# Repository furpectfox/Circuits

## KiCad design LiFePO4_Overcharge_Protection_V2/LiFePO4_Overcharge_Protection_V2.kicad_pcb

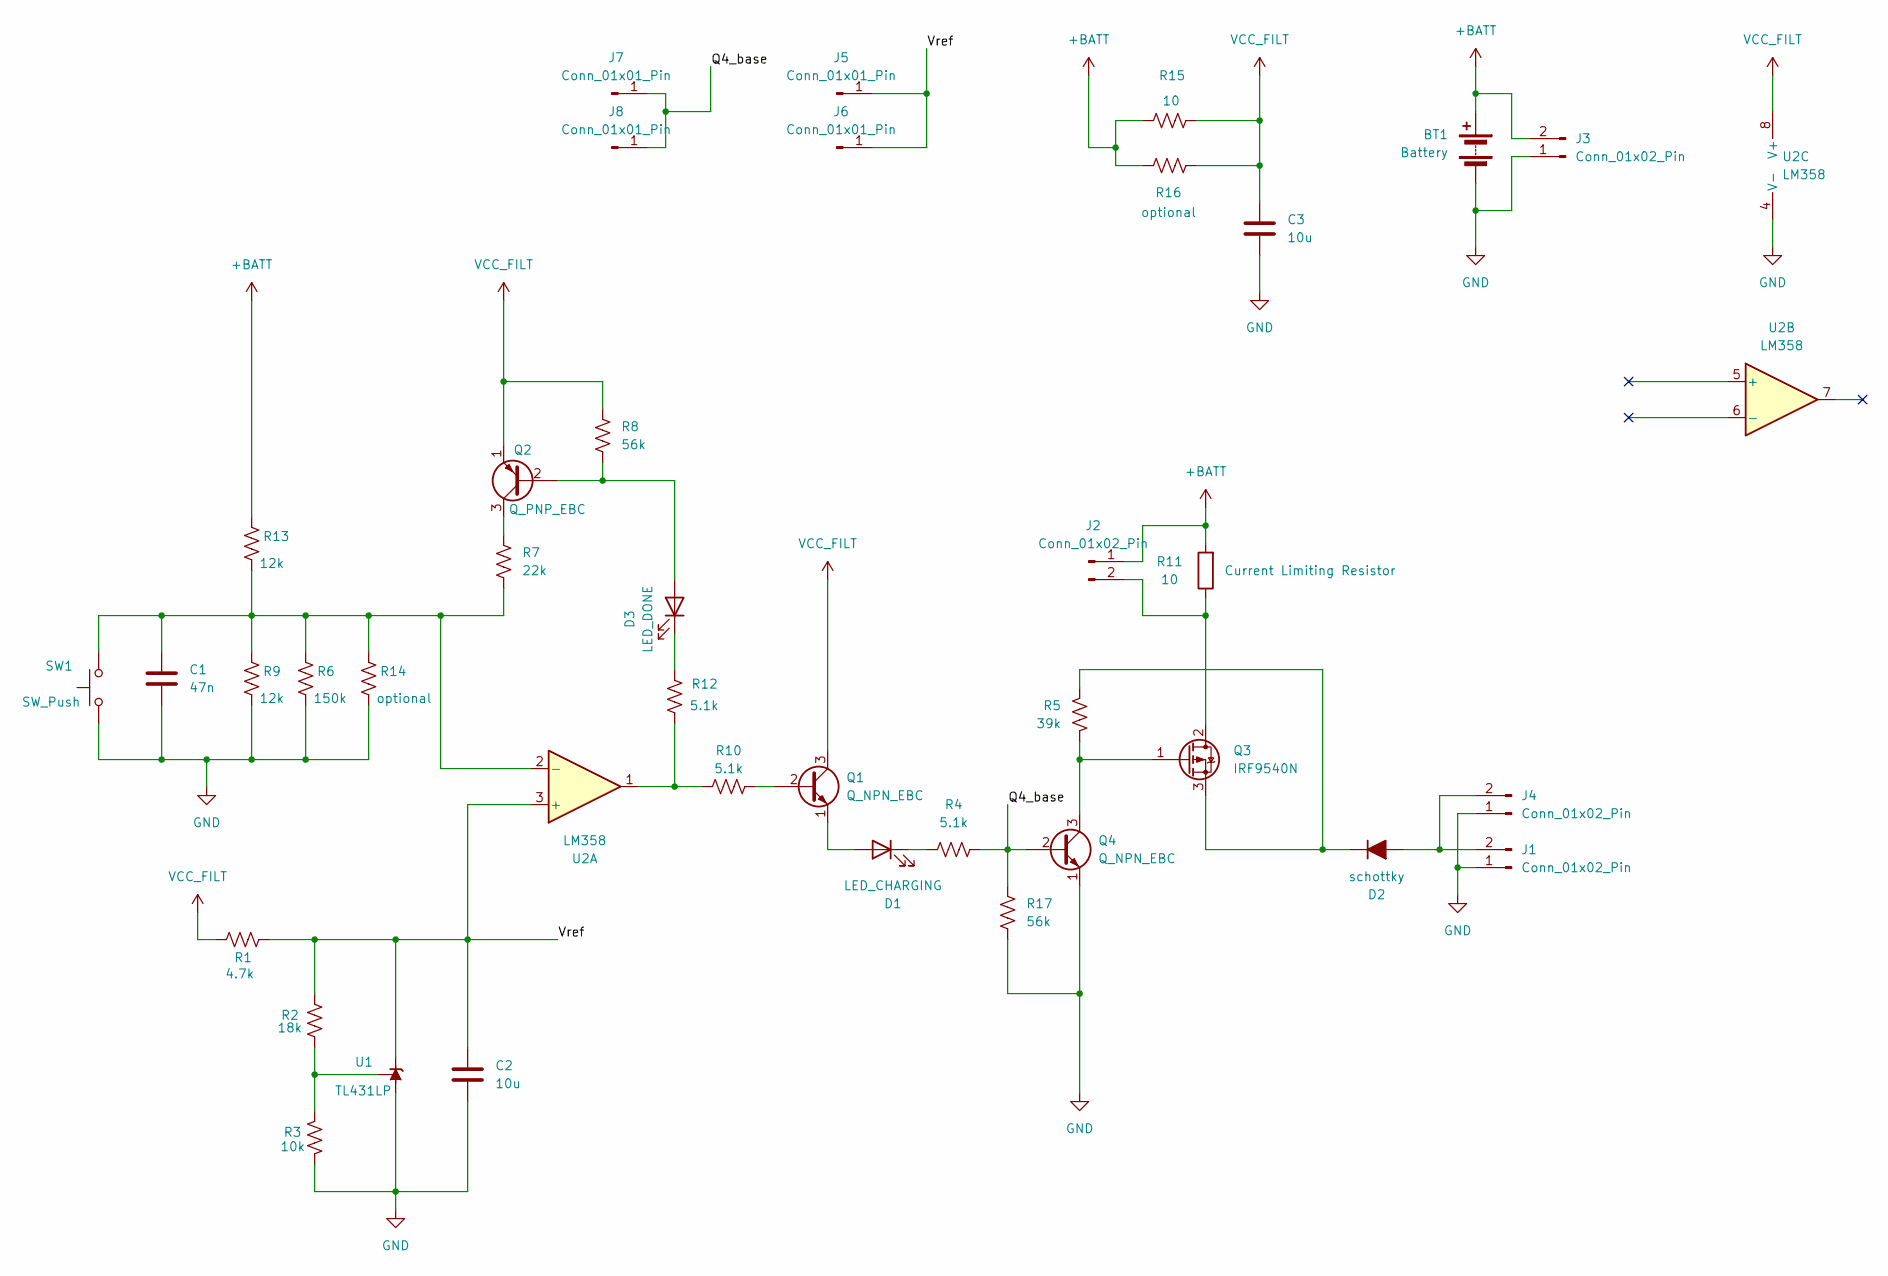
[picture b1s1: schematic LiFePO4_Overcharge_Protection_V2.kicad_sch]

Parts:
BT1: Battery; TestPoint_2Pads_Pitch5.08mm_Drill1.3mm
C1: 47n; C_Disc_D4.7mm_W2.5mm_P5.00mm
C2, C3: 10u; C_Disc_D4.7mm_W2.5mm_P5.00mm
D1: LED_CHARGING; LED_D5.0mm_Clear
D2: schottky; D_DO-27_P15.24mm_Horizontal
D3: LED_DONE; LED_D5.0mm_Clear
J1, J2, J3, J4: Conn_01x02_Pin; TestPoint_2Pads_Pitch5.08mm_Drill1.3mm
J5, J6, J7, J8: Conn_01x01_Pin; SolderWire-0.1sqmm_1x01_D0.4mm_OD1mm
Q1, Q4: Q_NPN_EBC; TO-92L_Inline_Wide
Q2: Q_PNP_EBC; TO-92L_Inline_Wide
Q3: IRF9540N; TO-220-3_Vertical
R1: 4.7k; R_Axial_DIN0207_L6.3mm_D2.5mm_P7.62mm_Horizontal
R2: 18k; R_Axial_DIN0207_L6.3mm_D2.5mm_P7.62mm_Horizontal
R3: 10k; R_Axial_DIN0207_L6.3mm_D2.5mm_P7.62mm_Horizontal
R4, R12: 5.1k; R_Axial_DIN0207_L6.3mm_D2.5mm_P7.62mm_Horizontal
R5: 39k; R_Axial_DIN0207_L6.3mm_D2.5mm_P7.62mm_Horizontal
R6: 150k; R_Axial_DIN0207_L6.3mm_D2.5mm_P7.62mm_Horizontal
R7: 22k; R_Axial_DIN0207_L6.3mm_D2.5mm_P7.62mm_Horizontal
R8, R17: 56k; R_Axial_DIN0207_L6.3mm_D2.5mm_P7.62mm_Horizontal
R9, R13: 12k; R_Axial_DIN0207_L6.3mm_D2.5mm_P7.62mm_Horizontal
R10: 5.1k; R_Axial_DIN0207_L6.3mm_D2.5mm_P10.16mm_Horizontal
R11: 10; TestPoint_2Pads_Pitch5.08mm_Drill1.3mm
R14, R16: optional; R_Axial_DIN0207_L6.3mm_D2.5mm_P7.62mm_Horizontal
R15: 10; R_Axial_DIN0207_L6.3mm_D2.5mm_P7.62mm_Horizontal
SW1: SW_Push
U1: TL431LP; TO-92L_Inline_Wide
U2: LM358; DIP-8_W7.62mm_LongPads

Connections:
+BATT: BT1.1 (+), J2.1, J3.2, R11.2, R13.1, R15.1, R16.1
/Q4_base: J7.1, J8.1, Q4.2 (B), R4.2, R17.1
/Vref: C2.1, J5.1, J6.1, R1.1, R2.1, U1.3 (K), U2.3 (+)
GND: BT1.2 (-), C1.2, C2.2, C3.2, J1.1, J3.1, J4.1, Q4.1 (E), R3.2, R6.2, R9.2, R14.2, R17.2, SW1.1, U1.2 (A), U2.4 (V-)
unnamed: D1.2 (A), Q1.1 (E)
unnamed: D1.1 (K), R4.1
unnamed: D2.2 (A), J1.2, J4.2
unnamed: D2.1 (K), Q3.3 (S), R5.2
unnamed: D3.2 (A), Q2.2 (B), R8.2
unnamed: D3.1 (K), R12.2
unnamed: J2.2, Q3.2 (D), R11.1
unnamed: Q1.2 (B), R10.2
unnamed: Q2.3 (C), R7.1
unnamed: Q3.1 (G), Q4.3 (C), R5.1
unnamed: R10.1, R12.1, U2.1
unnamed: R2.2, R3.1, U1.1 (REF)
unnamed: C1.1, R6.1, R7.2, R9.1, R13.2, R14.1, SW1.2, U2.2 (-)
VCC_FILT: C3.1, Q1.3 (C), Q2.1 (E), R1.2, R8.1, R15.2, R16.2, U2.8 (V+)

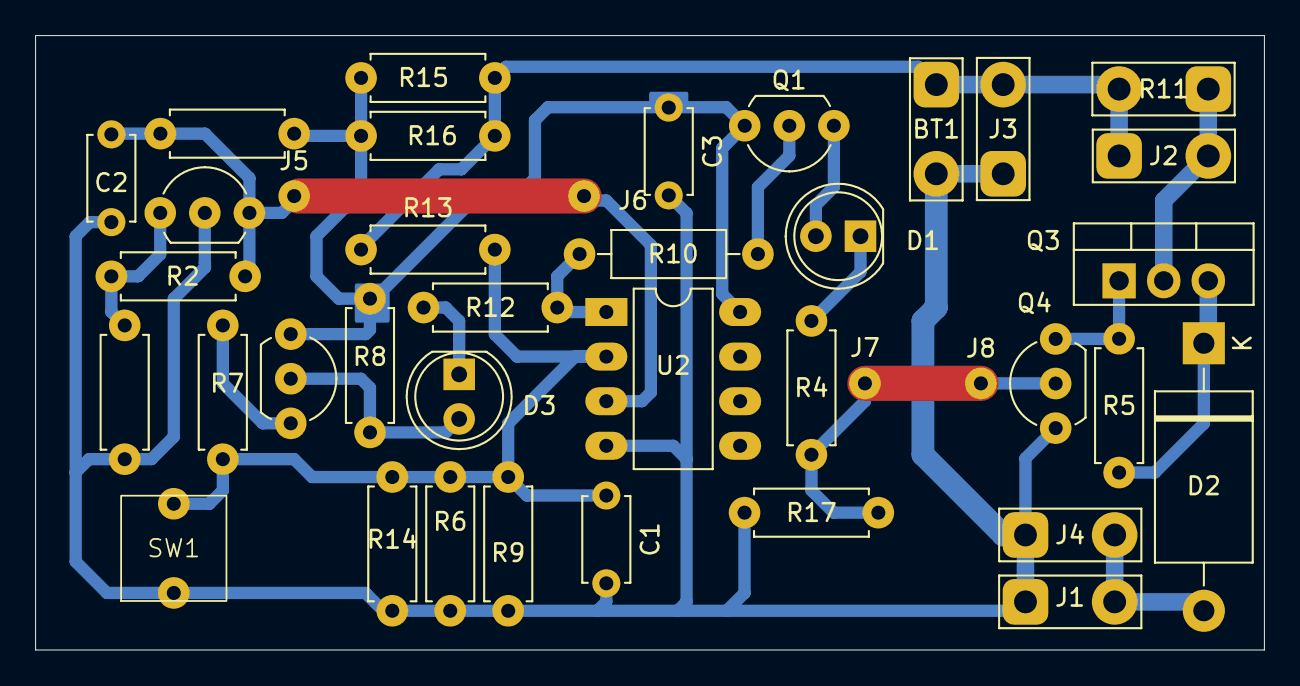
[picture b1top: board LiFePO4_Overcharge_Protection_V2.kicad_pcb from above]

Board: 2 copper layers, 70.0 x 35.0 mm, 39 parts (0 on the bottom side), 18 nets.

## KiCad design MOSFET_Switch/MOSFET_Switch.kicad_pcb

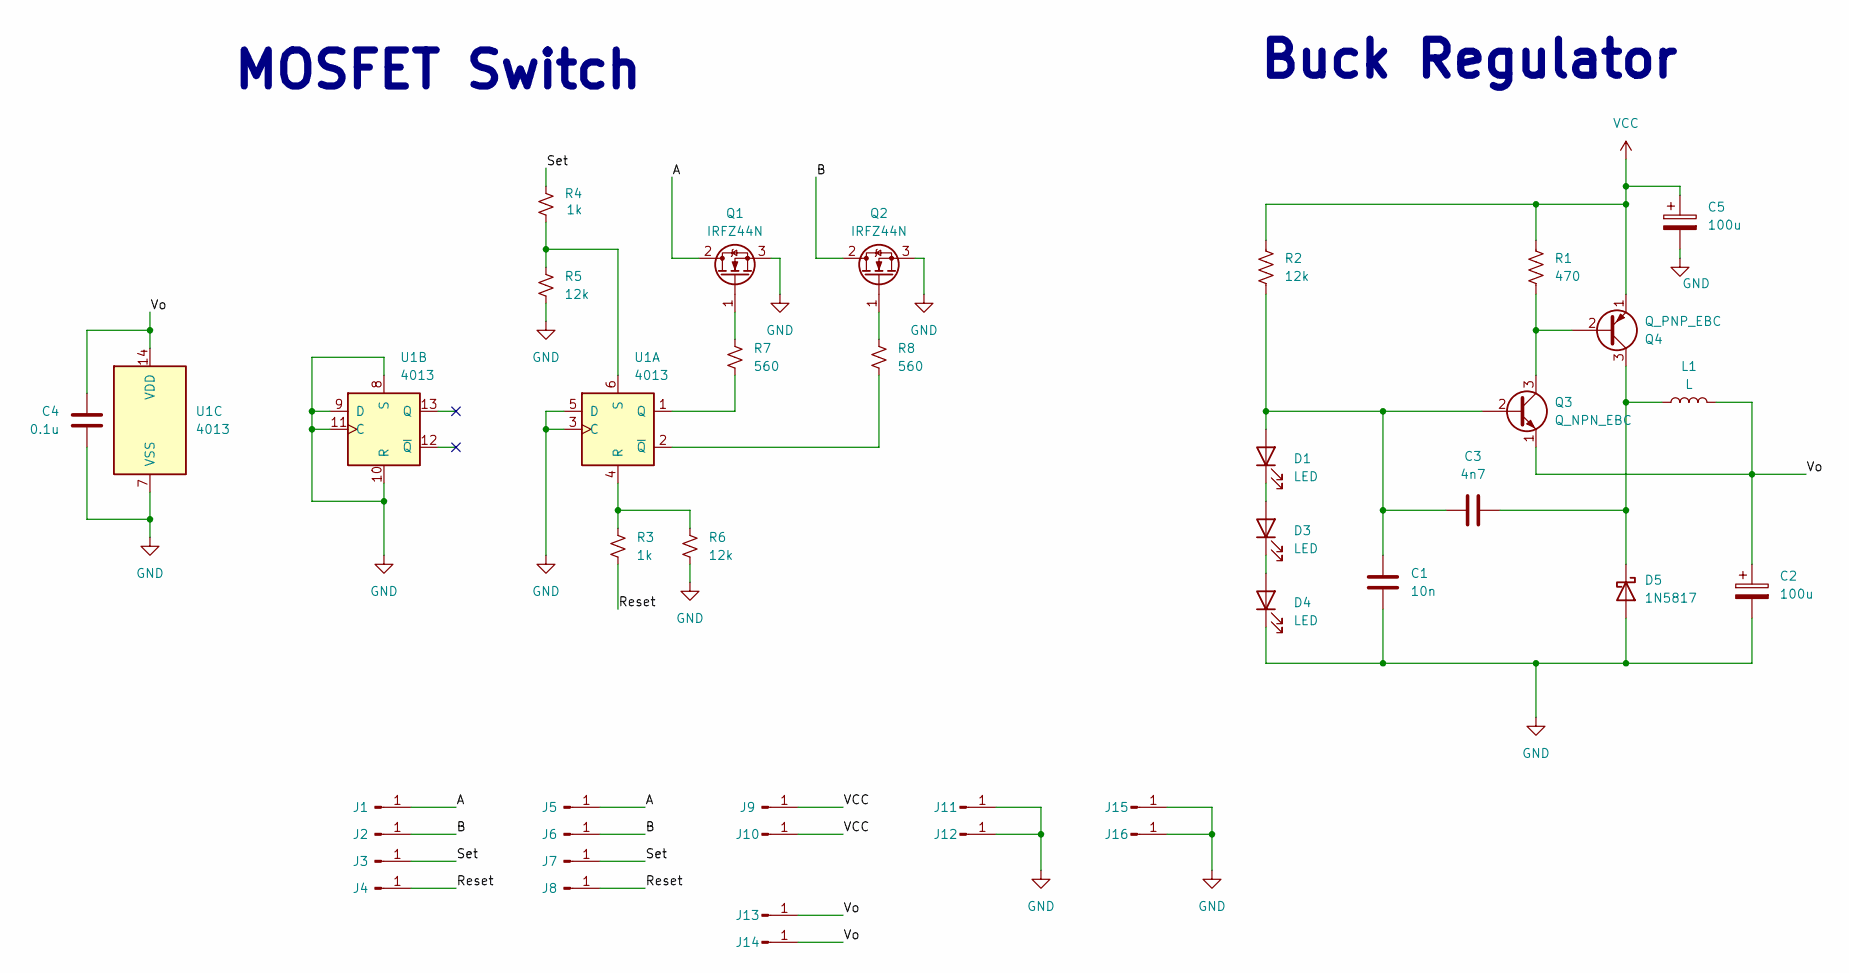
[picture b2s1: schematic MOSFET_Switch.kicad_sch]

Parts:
C1: 10n; C_Disc_D5.1mm_W3.2mm_P5.00mm
C2, C5: 100u; CP_Radial_D5.0mm_P2.50mm
C3: 4n7; C_Disc_D5.1mm_W3.2mm_P5.00mm
C4: 0.1u; C_Disc_D5.1mm_W3.2mm_P5.00mm
D1, D3, D4: LED; LED_D5.0mm
D5: 1N5817; D_DO-41_SOD81_P10.16mm_Horizontal
J1, J2, J3, J4, J5, J6, J7, J8, J9, J10, J11, J12, J13, J14, J15, J16: Conn_01x01_Pin; SolderWire-0.1sqmm_1x01_D0.4mm_OD1mm
L1: L; L_Radial_D7.0mm_P3.00mm
Q1, Q2: IRFZ44N; TO-220-3_Vertical
Q3: Q_NPN_EBC; TO-92L_Inline_Wide
Q4: Q_PNP_EBC; TO-92L_Inline_Wide
R1: 470; R_Axial_DIN0207_L6.3mm_D2.5mm_P7.62mm_Horizontal
R2: 12k; R_Axial_DIN0207_L6.3mm_D2.5mm_P7.62mm_Horizontal
R3, R4: 1k; R_0603_1608Metric_Pad0.98x0.95mm_HandSolder
R5, R6: 12k; R_0603_1608Metric_Pad0.98x0.95mm_HandSolder
R7, R8: 560; R_0603_1608Metric_Pad0.98x0.95mm_HandSolder
U1: 4013; DIP-14_W7.62mm_LongPads

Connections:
/A: J1.1, J5.1, Q1.2 (D)
/B: J2.1, J6.1, Q2.2 (D)
/Reset: J4.1, J8.1, R3.2
/Set: J3.1, J7.1, R4.1
/Vo: C2.1, C4.1, J13.1, J14.1, L1.2, Q3.1 (E), U1.14 (VDD)
GND: C1.2, C2.2, C4.2, C5.2, D4.1 (K), D5.2 (A), J11.1, J12.1, J15.1, J16.1, Q1.3 (S), Q2.3 (S), R5.2, R6.2, U1.3 (C), U1.5 (D), U1.7 (VSS), U1.8 (S), U1.9 (D), U1.10 (R), U1.11 (C)
unnamed: C1.1, C3.1, D1.2 (A), Q3.2 (B), R2.2
unnamed: D1.1 (K), D3.2 (A)
unnamed: D3.1 (K), D4.2 (A)
unnamed: C3.2, D5.1 (K), L1.1, Q4.3 (C)
unnamed: Q1.1 (G), R7.1
unnamed: Q2.1 (G), R8.1
unnamed: Q3.3 (C), Q4.2 (B), R1.2
unnamed: R7.2, U1.1 (Q)
unnamed: R3.1, R6.1, U1.4 (R)
unnamed: R4.2, R5.1, U1.6 (S)
unnamed: R8.2, U1.2 (~Q)
VCC: C5.1, J9.1, J10.1, Q4.1 (E), R1.1, R2.1

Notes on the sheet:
Buck Regulator
MOSFET Switch

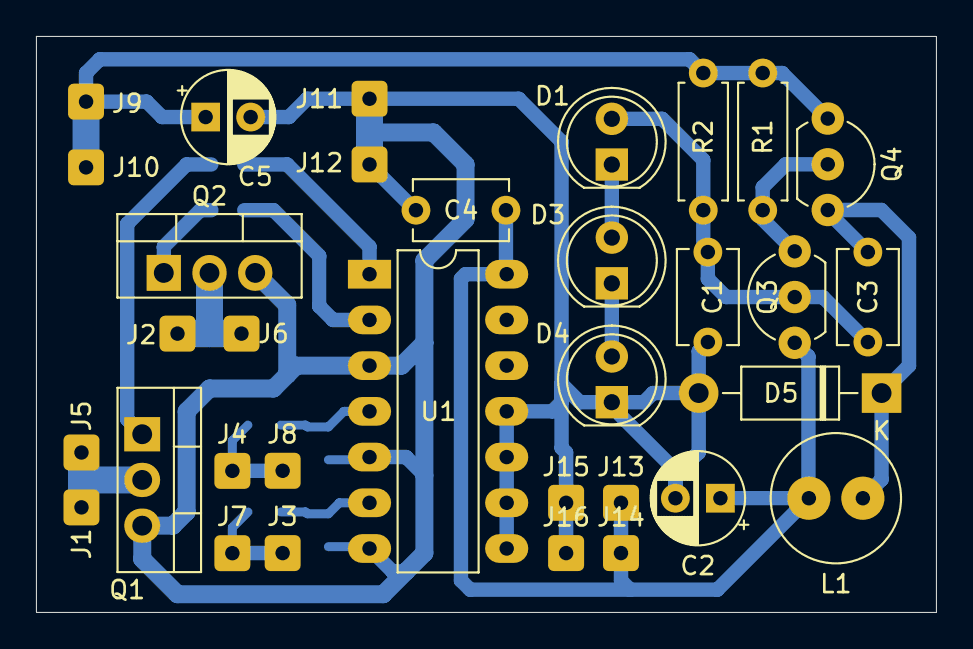
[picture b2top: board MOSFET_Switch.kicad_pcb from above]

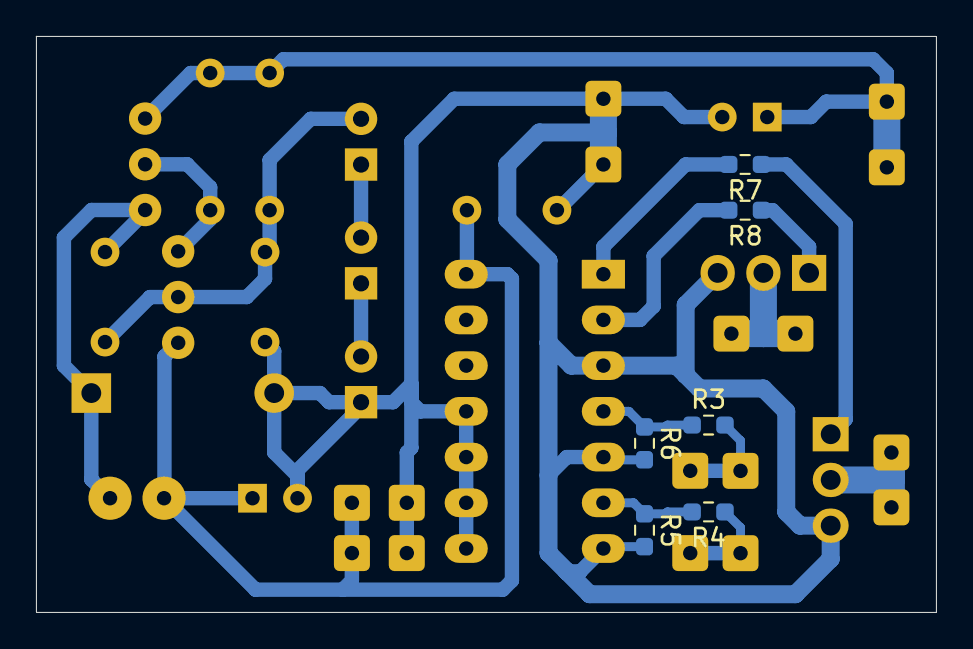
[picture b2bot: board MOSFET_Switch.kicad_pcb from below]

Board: 2 copper layers, 50.0 x 32.0 mm, 39 parts (6 on the bottom side), 18 nets.

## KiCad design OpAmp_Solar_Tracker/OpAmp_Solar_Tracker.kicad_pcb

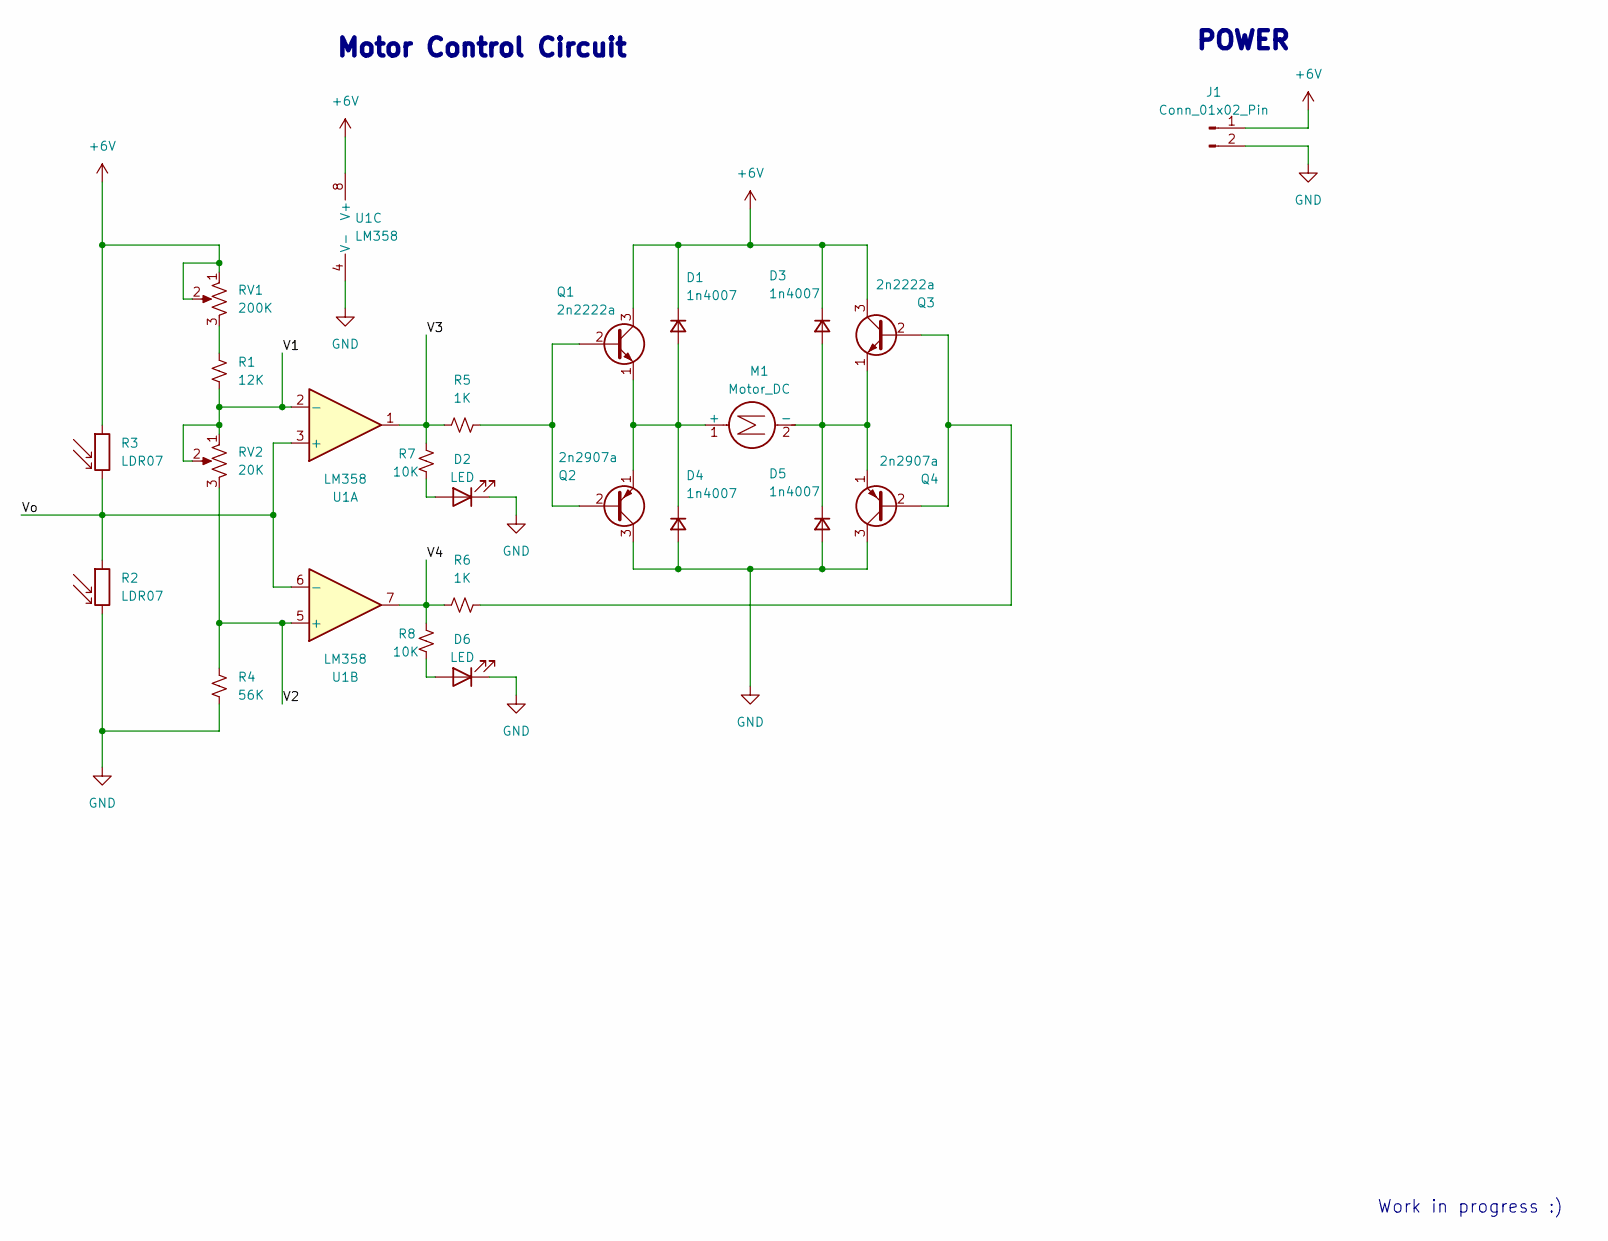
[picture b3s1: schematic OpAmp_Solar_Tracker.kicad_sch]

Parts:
D1, D3, D4, D5: 1n4007; D_A-405_P7.62mm_Horizontal
D2, D6: LED; LED_D5.0mm
J1: Conn_01x02_Pin; PinHeader_1x02_P2.54mm_Vertical
M1: Motor_DC; TerminalBlock_Altech_AK300-2_P5.00mm
Q1, Q3: 2n2222a; TO-92L_Inline_Wide
Q2, Q4: 2n2907a; TO-92L_Inline_Wide
R1: 12K; R_Axial_DIN0207_L6.3mm_D2.5mm_P7.62mm_Horizontal
R2, R3: LDR07; TerminalBlock_Altech_AK300-2_P5.00mm
R4: 56K; R_Axial_DIN0207_L6.3mm_D2.5mm_P7.62mm_Horizontal
R5, R6: 1K; R_Axial_DIN0207_L6.3mm_D2.5mm_P7.62mm_Horizontal
R7, R8: 10K; R_Axial_DIN0207_L6.3mm_D2.5mm_P7.62mm_Horizontal
RV1: 200K; BOJACK_Potentiometer
RV2: 20K; BOJACK_Potentiometer
U1: LM358; DIP-8_W7.62mm

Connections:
+6V: D1.1 (K), D3.1 (K), J1.1, Q1.3 (C), Q3.3 (C), RV1.1, RV1.2, U1.8 (V+); also elsewhere on the board
/V1: R1.2, RV2.1, RV2.2, U1.2 (-)
/V2: R4.1, RV2.3, U1.5 (+)
/V3: R5.1, R7.2, U1.1
/V4: R6.1, R8.2, U1.7
/Vo: U1.3 (+), U1.6 (-); also elsewhere on the board
GND: D2.1 (K), D4.2 (A), D5.2 (A), D6.1 (K), J1.2, Q2.3 (C), Q4.3 (C), R4.2, U1.4 (V-); also elsewhere on the board
unnamed: D1.2 (A), D4.1 (K), M1.1 (+), Q1.1 (E), Q2.1 (E)
unnamed: D2.2 (A), R7.1
unnamed: D3.2 (A), D5.1 (K), M1.2 (-), Q3.1 (E), Q4.1 (E)
unnamed: D6.2 (A), R8.1
unnamed: Q1.2 (B), Q2.2 (B), R5.2
unnamed: Q3.2 (B), Q4.2 (B), R6.2
unnamed: R1.1, RV1.3

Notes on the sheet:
Motor Control Circuit
POWER
Work in progress :)

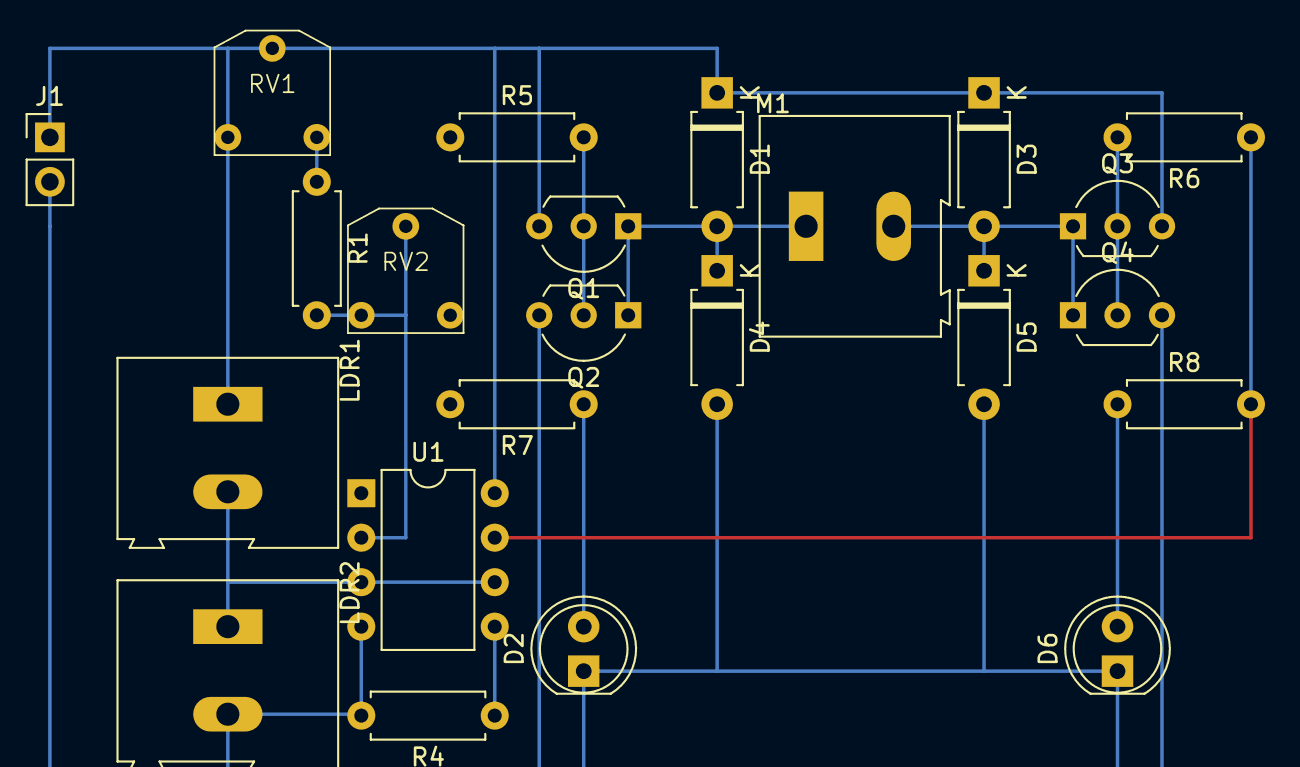
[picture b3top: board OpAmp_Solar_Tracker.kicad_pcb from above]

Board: 2 copper layers, 23 parts (0 on the bottom side), 14 nets.

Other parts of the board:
LDR1, LDR2: LDR07; TerminalBlock_Altech_AK300-2_P5.00mm

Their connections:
+6V: LDR1.1; also elsewhere on the board
/Vo: LDR1.2, LDR2.1; also elsewhere on the board
GND: LDR2.2; also elsewhere on the board

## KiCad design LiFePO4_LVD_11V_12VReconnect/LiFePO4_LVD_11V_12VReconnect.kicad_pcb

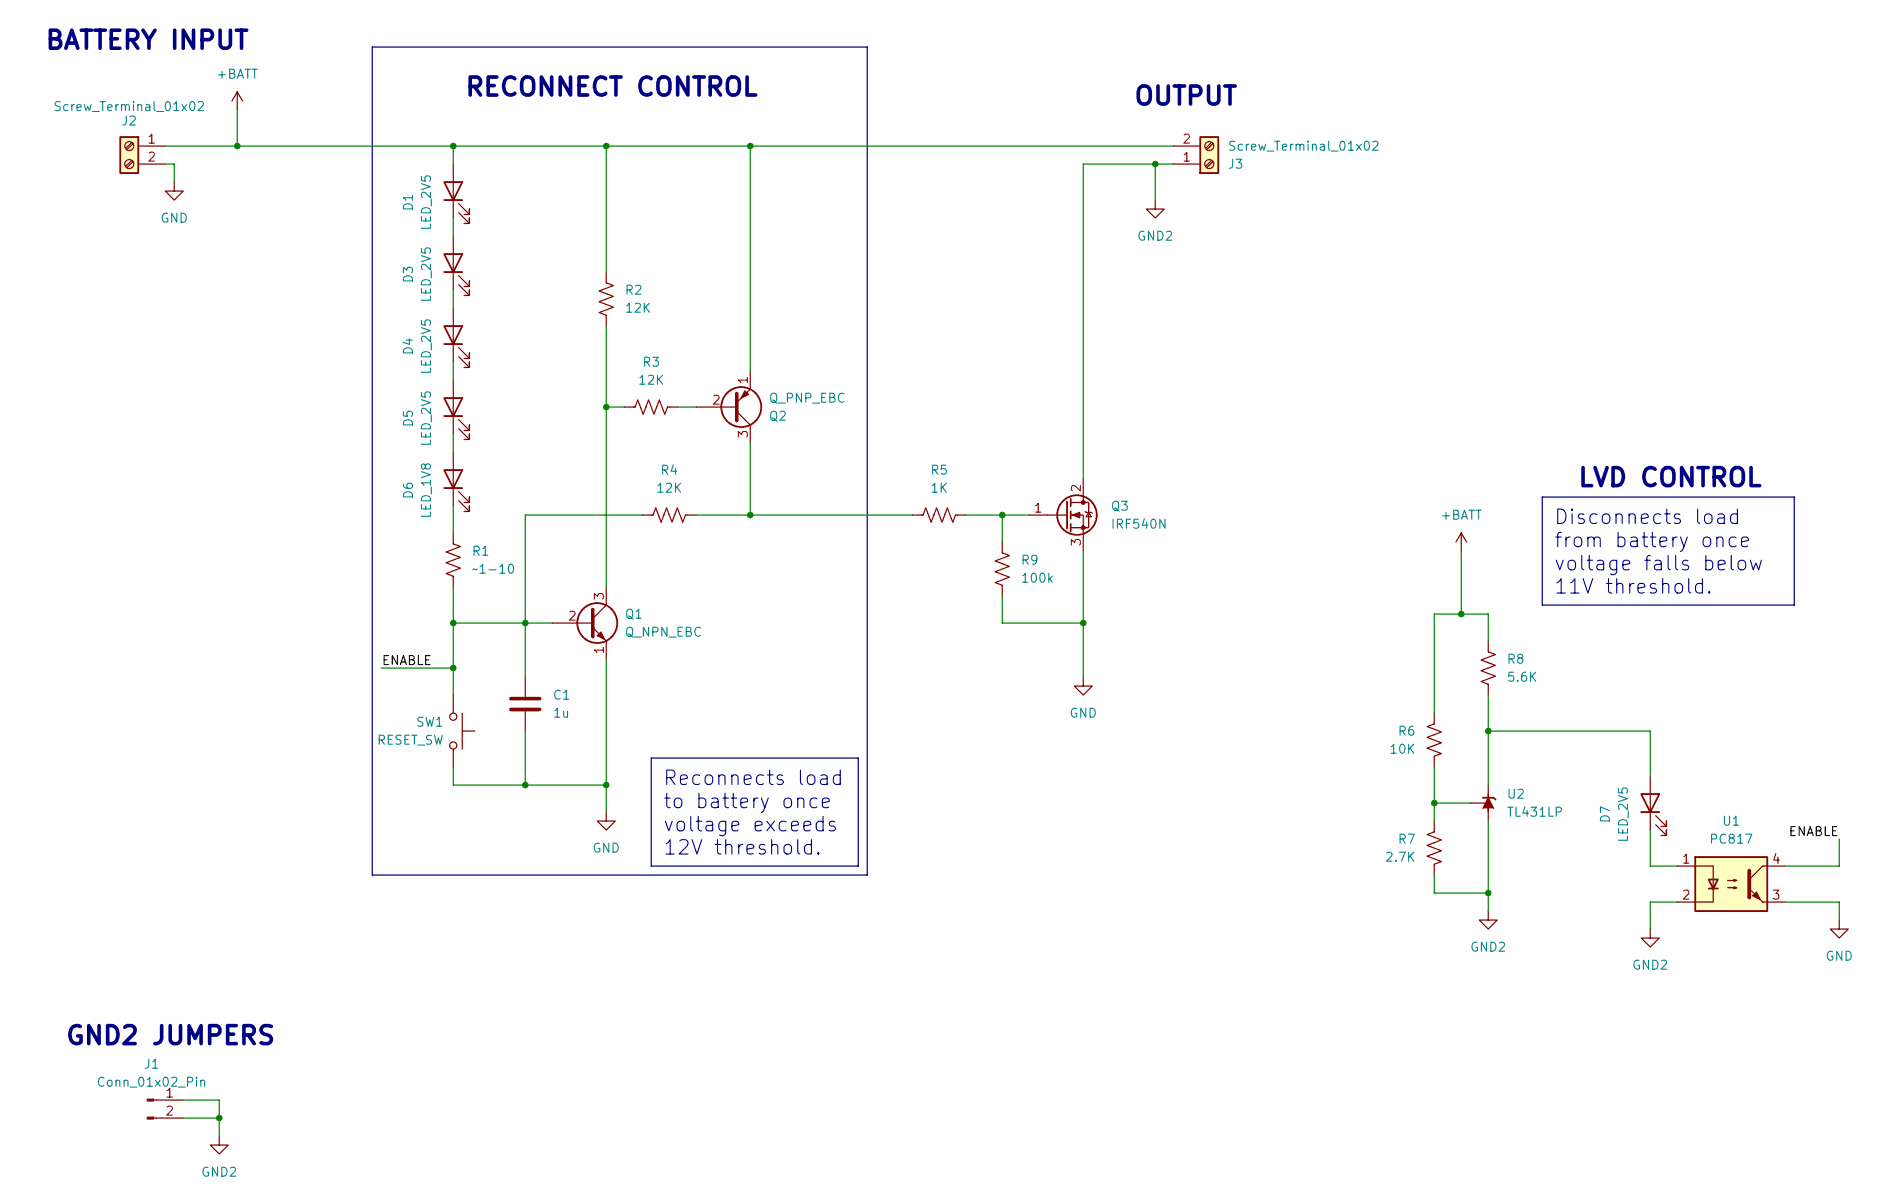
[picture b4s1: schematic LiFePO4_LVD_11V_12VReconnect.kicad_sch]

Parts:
C1: 1u; C_Disc_D5.1mm_W3.2mm_P5.00mm
D1, D3, D4, D5, D7: LED_2V5; LED_D5.0mm
D6: LED_1V8; LED_D5.0mm
J1: Conn_01x02_Pin; SolderWire-0.75sqmm_1x02_P7mm_D1.25mm_OD3.5mm
J2, J3: Screw_Terminal_01x02; TerminalBlock_Altech_AK300-2_P5.00mm
Q1: Q_NPN_EBC; TO-92_Inline_Wide
Q2: Q_PNP_EBC; TO-92_Inline_Wide
Q3: IRF540N; TO-220-3_Vertical
R1: ~1-10; R_Axial_DIN0207_L6.3mm_D2.5mm_P7.62mm_Horizontal
R2, R3, R4: 12K; R_Axial_DIN0207_L6.3mm_D2.5mm_P7.62mm_Horizontal
R5: 1K; R_Axial_DIN0207_L6.3mm_D2.5mm_P7.62mm_Horizontal
R6: 10K; R_Axial_DIN0207_L6.3mm_D2.5mm_P7.62mm_Horizontal
R7: 2.7K; R_Axial_DIN0207_L6.3mm_D2.5mm_P7.62mm_Horizontal
R8: 5.6K; R_Axial_DIN0207_L6.3mm_D2.5mm_P7.62mm_Horizontal
R9: 100k; R_Axial_DIN0207_L6.3mm_D2.5mm_P7.62mm_Horizontal
SW1: RESET_SW; SolderWire-0.75sqmm_1x02_P4.8mm_D1.25mm_OD2.3mm
U1: PC817; DIP-4_W7.62mm
U2: TL431LP; TO-92_Inline_Wide

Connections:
+BATT: D1.2 (A), J2.1, J3.2, Q2.1 (E), R2.1, R6.2, R8.2
/ENABLE: C1.1, Q1.2 (B), R1.2, R4.1, SW1.2, U1.4
GND: C1.2, J2.2, Q1.1 (E), Q3.3 (S), R9.1, SW1.1, U1.3
GND2: J1.1, J1.2, J3.1, Q3.2 (D), R7.1, U1.2, U2.2 (A)
unnamed: D1.1 (K), D3.2 (A)
unnamed: D3.1 (K), D4.2 (A)
unnamed: D4.1 (K), D5.2 (A)
unnamed: D5.1 (K), D6.2 (A)
unnamed: D6.1 (K), R1.1
unnamed: D7.2 (A), R8.1, U2.3 (K)
unnamed: D7.1 (K), U1.1
unnamed: Q1.3 (C), R2.2, R3.1
unnamed: Q2.2 (B), R3.2
unnamed: Q2.3 (C), R4.2, R5.1
unnamed: Q3.1 (G), R5.2, R9.2
unnamed: R6.1, R7.2, U2.1 (REF)

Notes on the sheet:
Reconnects load to battery once voltage exceeds 12V threshold.
Disconnects load from battery once voltage falls below 11V threshold.
LVD CONTROL
BATTERY INPUT
GND2 JUMPERS
RECONNECT CONTROL
OUTPUT

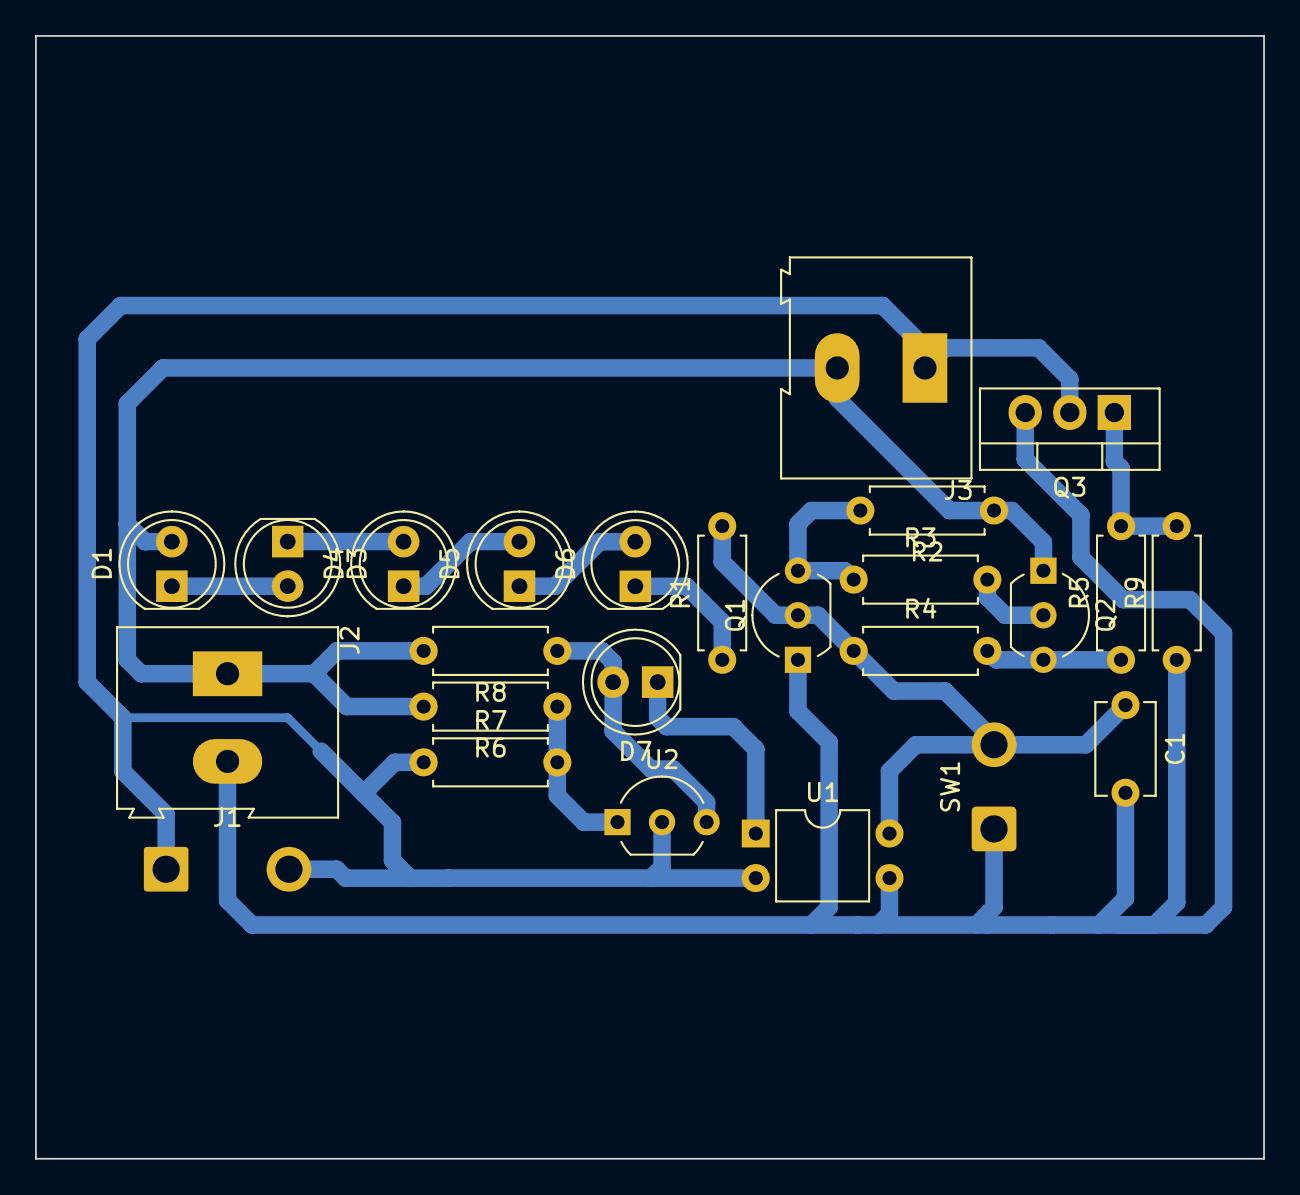
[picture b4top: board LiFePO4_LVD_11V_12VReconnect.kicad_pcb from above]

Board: 2 copper layers, 70.0 x 64.0 mm, 25 parts (0 on the bottom side), 16 nets.

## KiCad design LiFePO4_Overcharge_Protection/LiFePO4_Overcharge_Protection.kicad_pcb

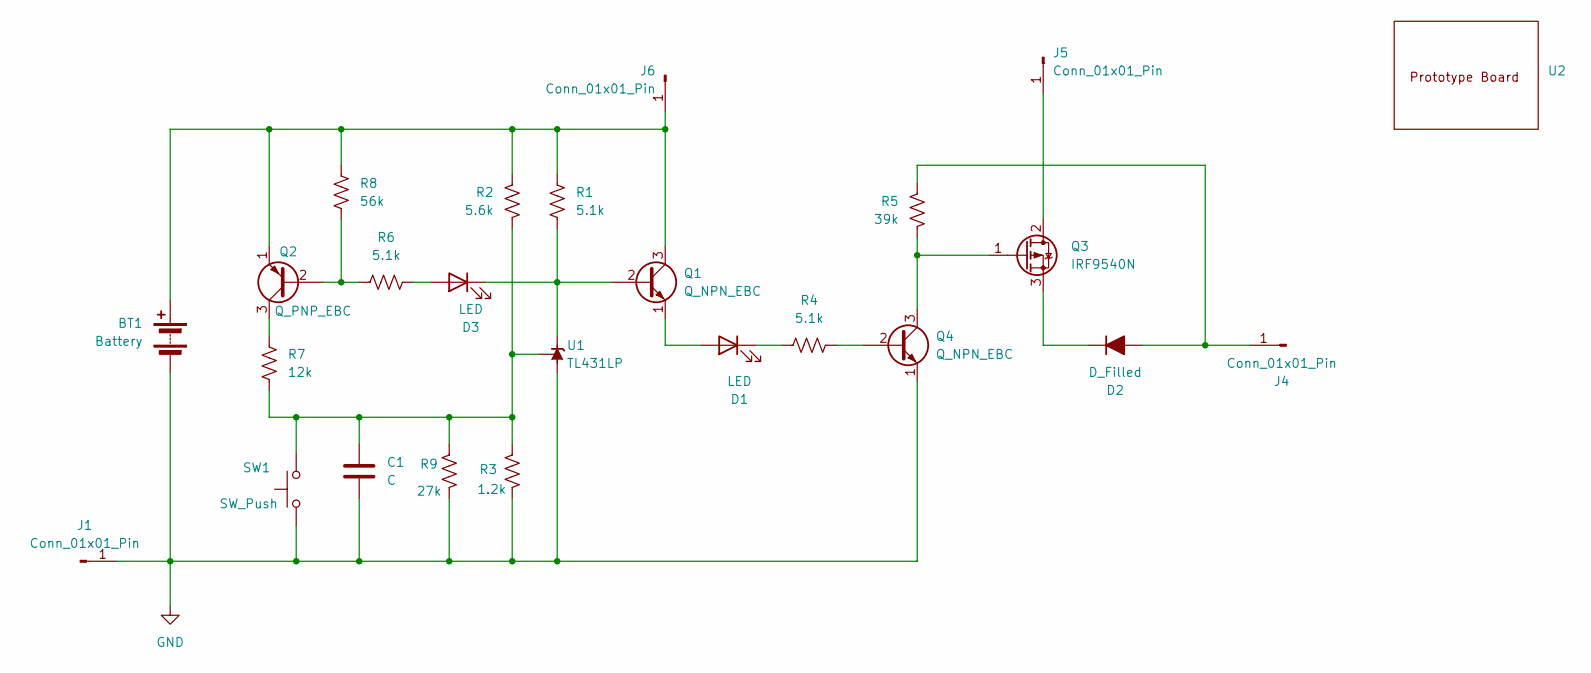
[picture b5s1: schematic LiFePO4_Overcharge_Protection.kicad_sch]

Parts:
BT1: Battery
C1: C; C_Disc_D3.8mm_W2.6mm_P2.50mm
D1, D3: LED; LED_D5.0mm_Clear
D2: D_Filled; D_DO-27_P15.24mm_Horizontal
J1, J4, J5, J6: Conn_01x01_Pin; PinHeader_1x01_P1.00mm_Vertical
Q1, Q4: Q_NPN_EBC; TO-92L_Inline_Wide
Q2: Q_PNP_EBC; TO-92L_Inline_Wide
Q3: IRF9540N; TO-220-3_Vertical
R1, R6: 5.1k; R_Axial_DIN0207_L6.3mm_D2.5mm_P10.16mm_Horizontal
R2: 5.6k; R_Axial_DIN0207_L6.3mm_D2.5mm_P15.24mm_Horizontal
R3: 1.2k; R_Axial_DIN0207_L6.3mm_D2.5mm_P10.16mm_Horizontal
R4: 5.1k; R_Axial_DIN0207_L6.3mm_D2.5mm_P7.62mm_Horizontal
R5: 39k; R_Axial_DIN0207_L6.3mm_D2.5mm_P7.62mm_Horizontal
R7: 12k; R_Axial_DIN0207_L6.3mm_D2.5mm_P7.62mm_Horizontal
R8: 56k; R_Axial_DIN0207_L6.3mm_D2.5mm_P10.16mm_Horizontal
R9: 27k; R_Axial_DIN0207_L6.3mm_D2.5mm_P10.16mm_Horizontal
SW1: SW_Push
U1: TL431LP; TO-92L_Inline_Wide
U2: Prototype_Board

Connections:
GND: BT1.2 (-), C1.2, J1.1, Q4.1 (E), R3.2, R9.2, SW1.1, U1.2 (A)
unnamed: BT1.1 (+), J6.1, Q1.3 (C), Q2.1 (E), R1.1, R2.1, R8.1
unnamed: D1.2 (A), Q1.1 (E)
unnamed: D1.1 (K), R4.1
unnamed: D2.2 (A), J4.1, R5.2
unnamed: D2.1 (K), Q3.3 (S)
unnamed: D3.2 (A), R6.1
unnamed: D3.1 (K), Q1.2 (B), R1.2, U1.3 (K)
unnamed: J5.1, Q3.2 (D)
unnamed: Q2.2 (B), R6.2, R8.2
unnamed: Q2.3 (C), R7.1
unnamed: Q3.1 (G), Q4.3 (C), R5.1
unnamed: Q4.2 (B), R4.2
unnamed: C1.1, R2.2, R3.1, R7.2, R9.1, SW1.2, U1.1 (REF)

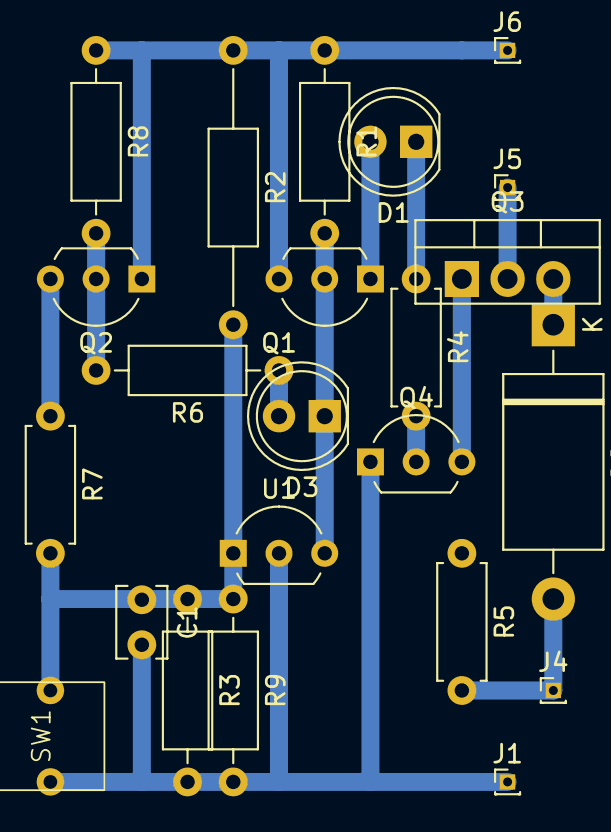
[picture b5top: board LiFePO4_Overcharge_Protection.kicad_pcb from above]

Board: 2 copper layers, 24 parts (0 on the bottom side), 14 nets.

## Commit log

2025-05-23 add LiFePO4_Overcharge_Protection_v2
2025-06-08 add LiFePO4_Overcharge_Protection_V2 and MOSFET_Switch
